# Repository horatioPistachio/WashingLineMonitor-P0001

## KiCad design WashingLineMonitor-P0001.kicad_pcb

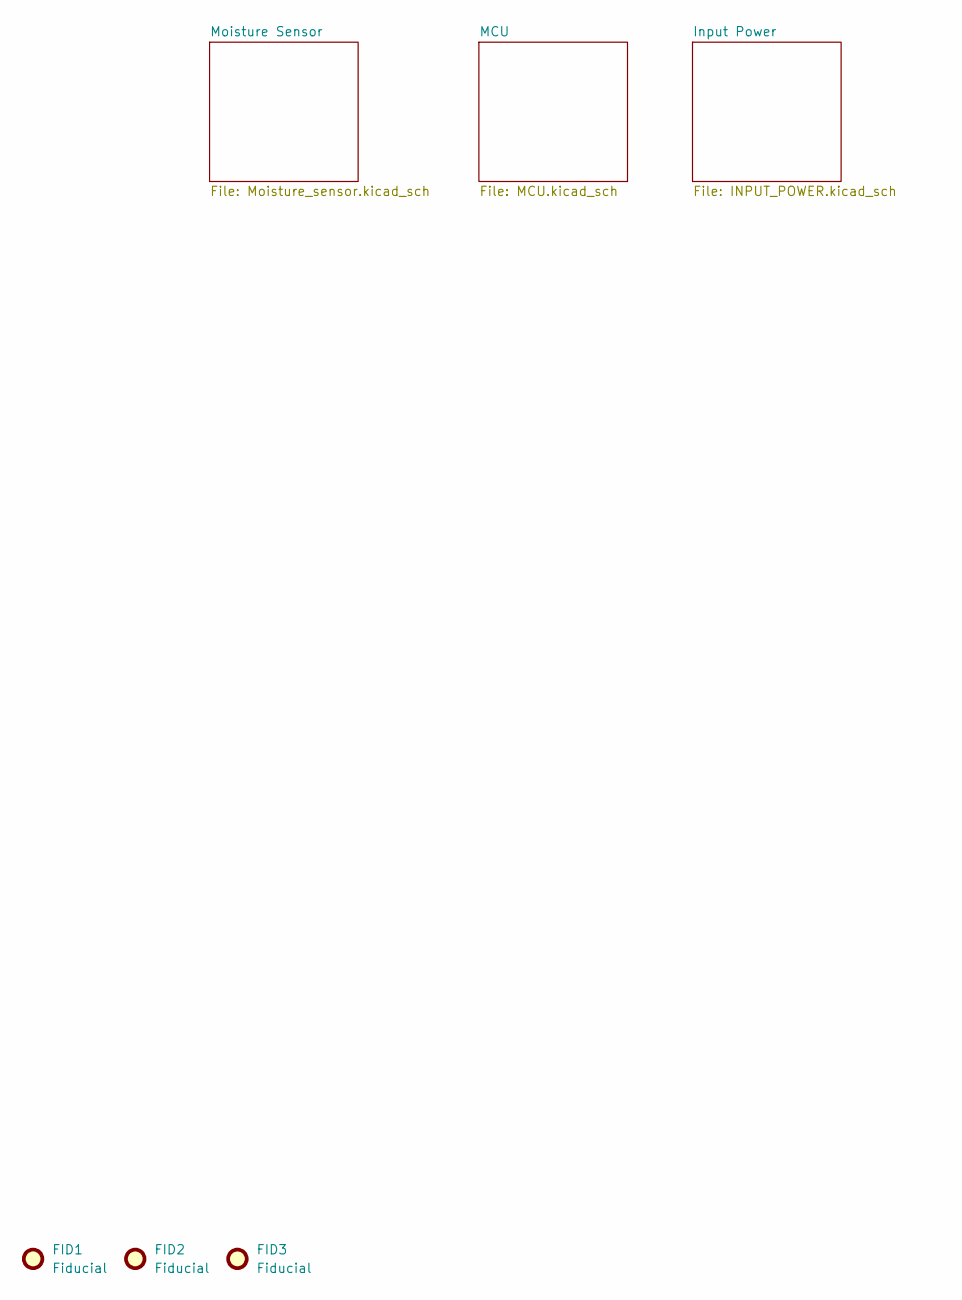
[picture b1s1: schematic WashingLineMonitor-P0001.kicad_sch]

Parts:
FID1, FID2, FID3: Fiducial; Fiducial_0.5mm_Mask1mm

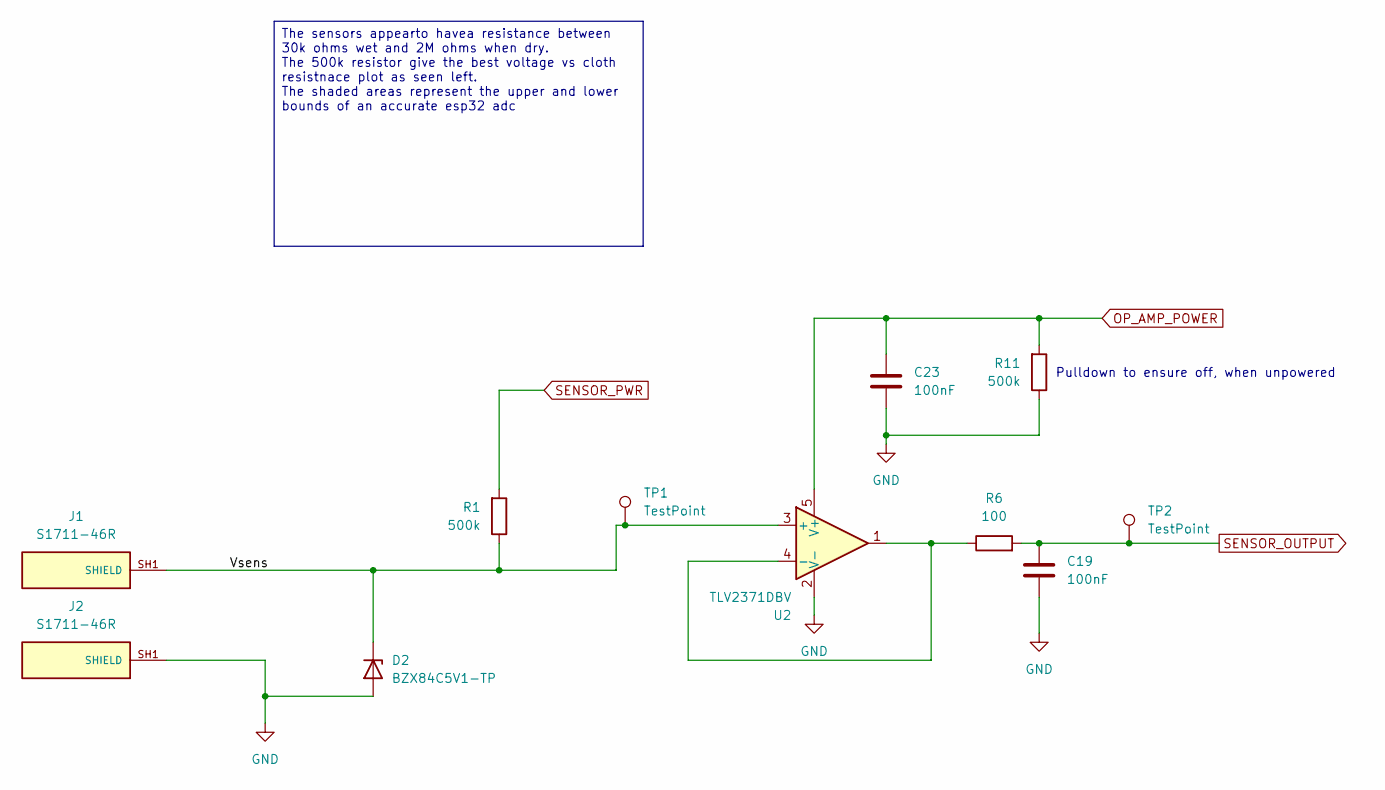
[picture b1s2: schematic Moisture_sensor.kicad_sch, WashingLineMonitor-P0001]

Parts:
C19, C23: 100nF; C_0805_2012Metric_Pad1.18x1.45mm_HandSolder
D2: BZX84C5V1-TP; SOT-23
J1, J2: S1711-46R; HARWIN_S1711-46R; PARTREV 8
R1, R11: 500k; R_0805_2012Metric_Pad1.20x1.40mm_HandSolder
R6: 100; R_0805_2012Metric_Pad1.20x1.40mm_HandSolder
TP1, TP2: TestPoint; TestPoint_Pad_D1.0mm
U2: TLV2371DBV; SOT-23-5

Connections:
/Moisture Sensor/Vsens: D2.3 (K), J1.SH1 (SHIELD_SH1), R1.1, TP1.1 (1_1), U2.3 (+)
GND: C19.2, C23.2, D2.1 (A), J2.SH1 (SHIELD_SH1), R11.1, U2.2 (V-); also elsewhere on the board
unnamed: R6.1, U2.1, U2.4 (-)
OP_AMP_POWER: C23.1, R11.2, U2.5 (V+); also elsewhere on the board
SENSOR_OUTPUT: C19.1, R6.2, TP2.1 (1_1); also elsewhere on the board
SENSOR_PWR: R1.2; also elsewhere on the board

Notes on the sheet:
Pulldown to ensure off, when unpowered
The sensors appearto havea resistance between 30k ohms wet and 2M ohms when dry. The 500k resistor give the best voltage vs cloth resistnace plot as seen left. The shaded areas represent the upper and lower bounds of an accurate esp32 adc

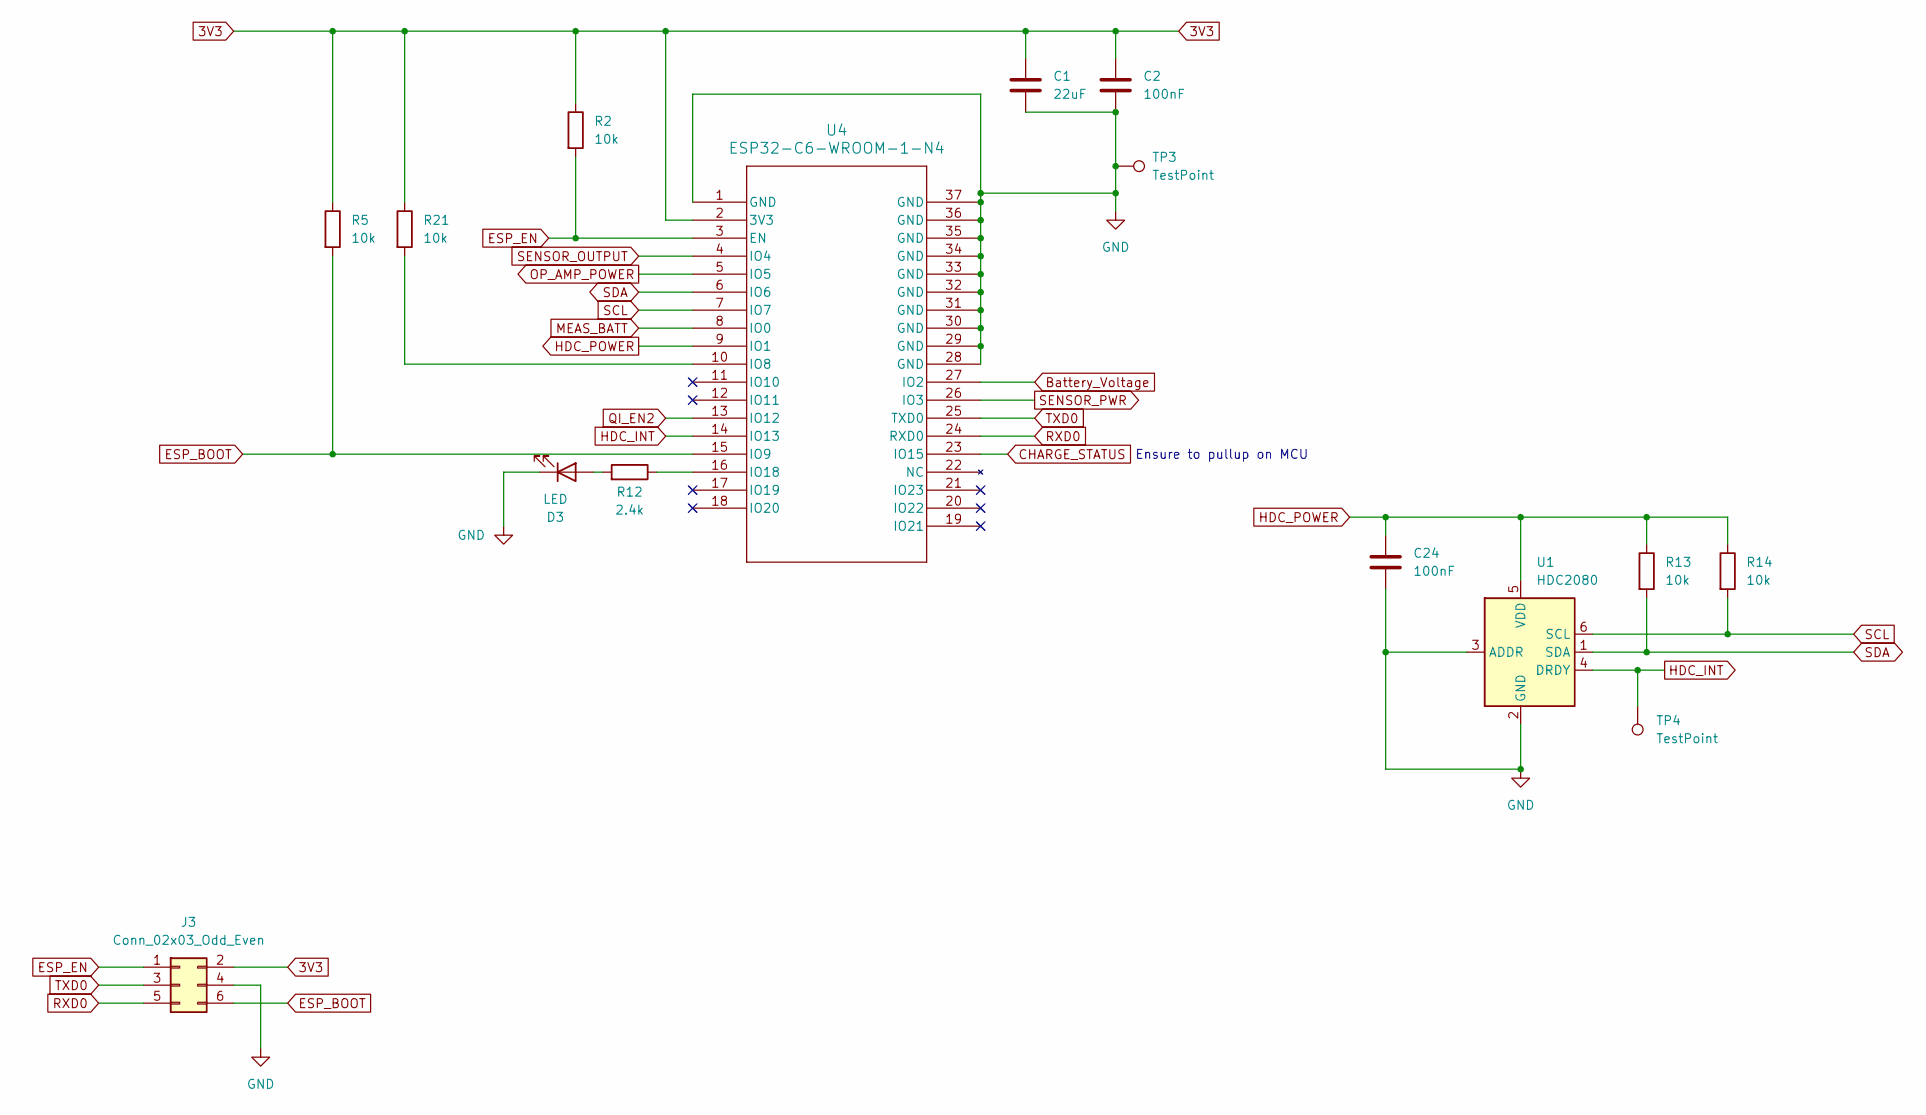
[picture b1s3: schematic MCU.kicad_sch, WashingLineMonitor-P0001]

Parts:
C1: 22uF; C_0805_2012Metric_Pad1.18x1.45mm_HandSolder
C2, C24: 100nF; C_0805_2012Metric_Pad1.18x1.45mm_HandSolder
D3: LED; LED_0805_2012Metric_Pad1.15x1.40mm_HandSolder
J3: Conn_02x03_Odd_Even; PinHeader_2x03_P1.27mm_Vertical_SMD; Digikey_Part_Number SAM13920TR-ND
R2, R5, R13, R14, R21: 10k; R_0805_2012Metric_Pad1.20x1.40mm_HandSolder
R12: 2.4k; R_0805_2012Metric_Pad1.20x1.40mm_HandSolder
TP3, TP4: TestPoint; TestPoint_Pad_D1.0mm
U1: HDC2080; Texas_S-PWSON-N6-HDC2080
U4: ESP32-C6-WROOM-1-N4; MOD28_ESP32-C6-WROOM-1_EXP

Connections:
3V3: C1.1, C2.1, J3.2, R2.1, R5.1, R21.1, U4.2 (3V3); also elsewhere on the board
Battery_Voltage: U4.27 (IO2); also elsewhere on the board
CHARGE_STATUS: U4.23 (IO15); also elsewhere on the board
ESP_BOOT: J3.6, R5.2, U4.15 (IO9)
ESP_EN: J3.1, R2.2, U4.3 (EN)
GND: C1.2, C2.2, C24.2, D3.1 (K), J3.4, TP3.1 (1_1), U1.2 (GND), U1.3 (ADDR), U4.1 (GND), U4.28 (GND), U4.29 (GND), U4.30 (GND), U4.31 (GND), U4.32 (GND), U4.33 (GND), U4.34 (GND), U4.35 (GND), U4.36 (GND), U4.37 (GND); also elsewhere on the board
HDC_INT: TP4.1 (1_1), U1.4 (DRDY), U4.14 (IO13)
HDC_POWER: C24.1, R13.1, R14.1, U1.5 (VDD), U4.9 (IO1)
MEAS_BATT: U4.8 (IO0); also elsewhere on the board
unnamed: D3.2 (A), R12.2
unnamed: R21.2, U4.10 (IO8)
unnamed: R12.1, U4.16 (IO18)
OP_AMP_POWER: U4.5 (IO5); also elsewhere on the board
QI_EN2: U4.13 (IO12); also elsewhere on the board
RXD0: J3.5, U4.24 (RXD0)
SCL: R14.2, U1.6 (SCL), U4.7 (IO7)
SDA: R13.2, U1.1 (SDA), U4.6 (IO6)
SENSOR_OUTPUT: U4.4 (IO4); also elsewhere on the board
SENSOR_PWR: U4.26 (IO3); also elsewhere on the board
TXD0: J3.3, U4.25 (TXD0)

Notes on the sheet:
Ensure to pullup on MCU

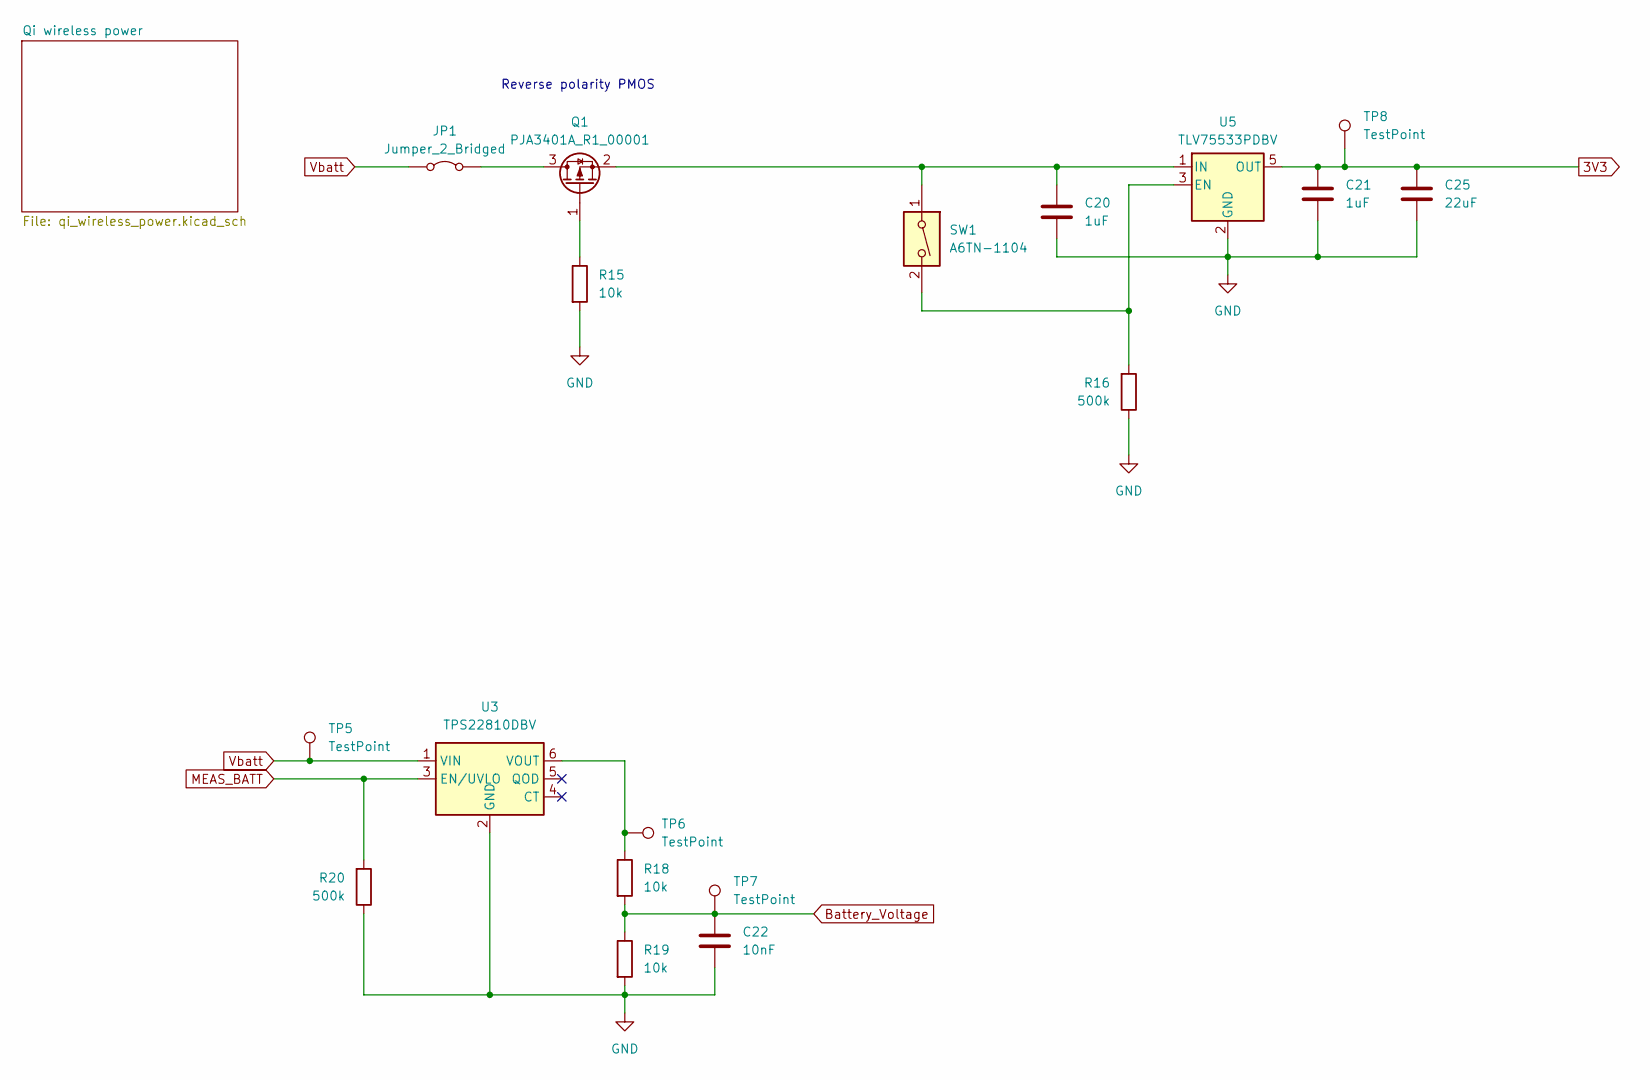
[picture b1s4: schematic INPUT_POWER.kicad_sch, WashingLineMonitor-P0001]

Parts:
C20, C21: 1uF; C_0805_2012Metric_Pad1.18x1.45mm_HandSolder
C22: 10nF; C_0805_2012Metric_Pad1.18x1.45mm_HandSolder
C25: 22uF; C_0805_2012Metric_Pad1.18x1.45mm_HandSolder
JP1: Jumper_2_Bridged; SolderJumper-2_P1.3mm_Bridged_RoundedPad1.0x1.5mm
Q1: PJA3401A_R1_00001; SOT-23
R15, R18, R19: 10k; R_0805_2012Metric_Pad1.20x1.40mm_HandSolder
R16, R20: 500k; R_0805_2012Metric_Pad1.20x1.40mm_HandSolder
SW1: A6TN-1104; SW_DIP_SPSTx01_Slide_6.7x4.1mm_W7.62mm_P2.54mm_LowProfile
TP5, TP6, TP7, TP8: TestPoint; TestPoint_Pad_D1.0mm
U3: TPS22810DBV; SOT-23-6
U5: TLV75533PDBV; SOT-23-5

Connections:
3V3: C21.2, C25.1, TP8.1 (1_1), U5.5 (OUT); also elsewhere on the board
Battery_Voltage: C22.1, R18.2, R19.1, TP7.1 (1_1); also elsewhere on the board
GND: C20.1, C21.1, C22.2, C25.2, R15.2, R16.1, R19.2, R20.1, U3.2 (GND), U5.2 (GND); also elsewhere on the board
MEAS_BATT: R20.2, U3.3 (EN/UVLO); also elsewhere on the board
unnamed: JP1.2 (B), Q1.3 (D)
unnamed: Q1.1 (G), R15.1
unnamed: C20.2, Q1.2 (S), SW1.1, U5.1 (IN)
unnamed: R18.1, TP6.1 (1_1), U3.6 (VOUT)
unnamed: R16.2, SW1.2, U5.3 (EN)
Vbatt: JP1.1 (A), TP5.1 (1_1), U3.1 (VIN); also elsewhere on the board

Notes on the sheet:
Reverse polarity PMOS

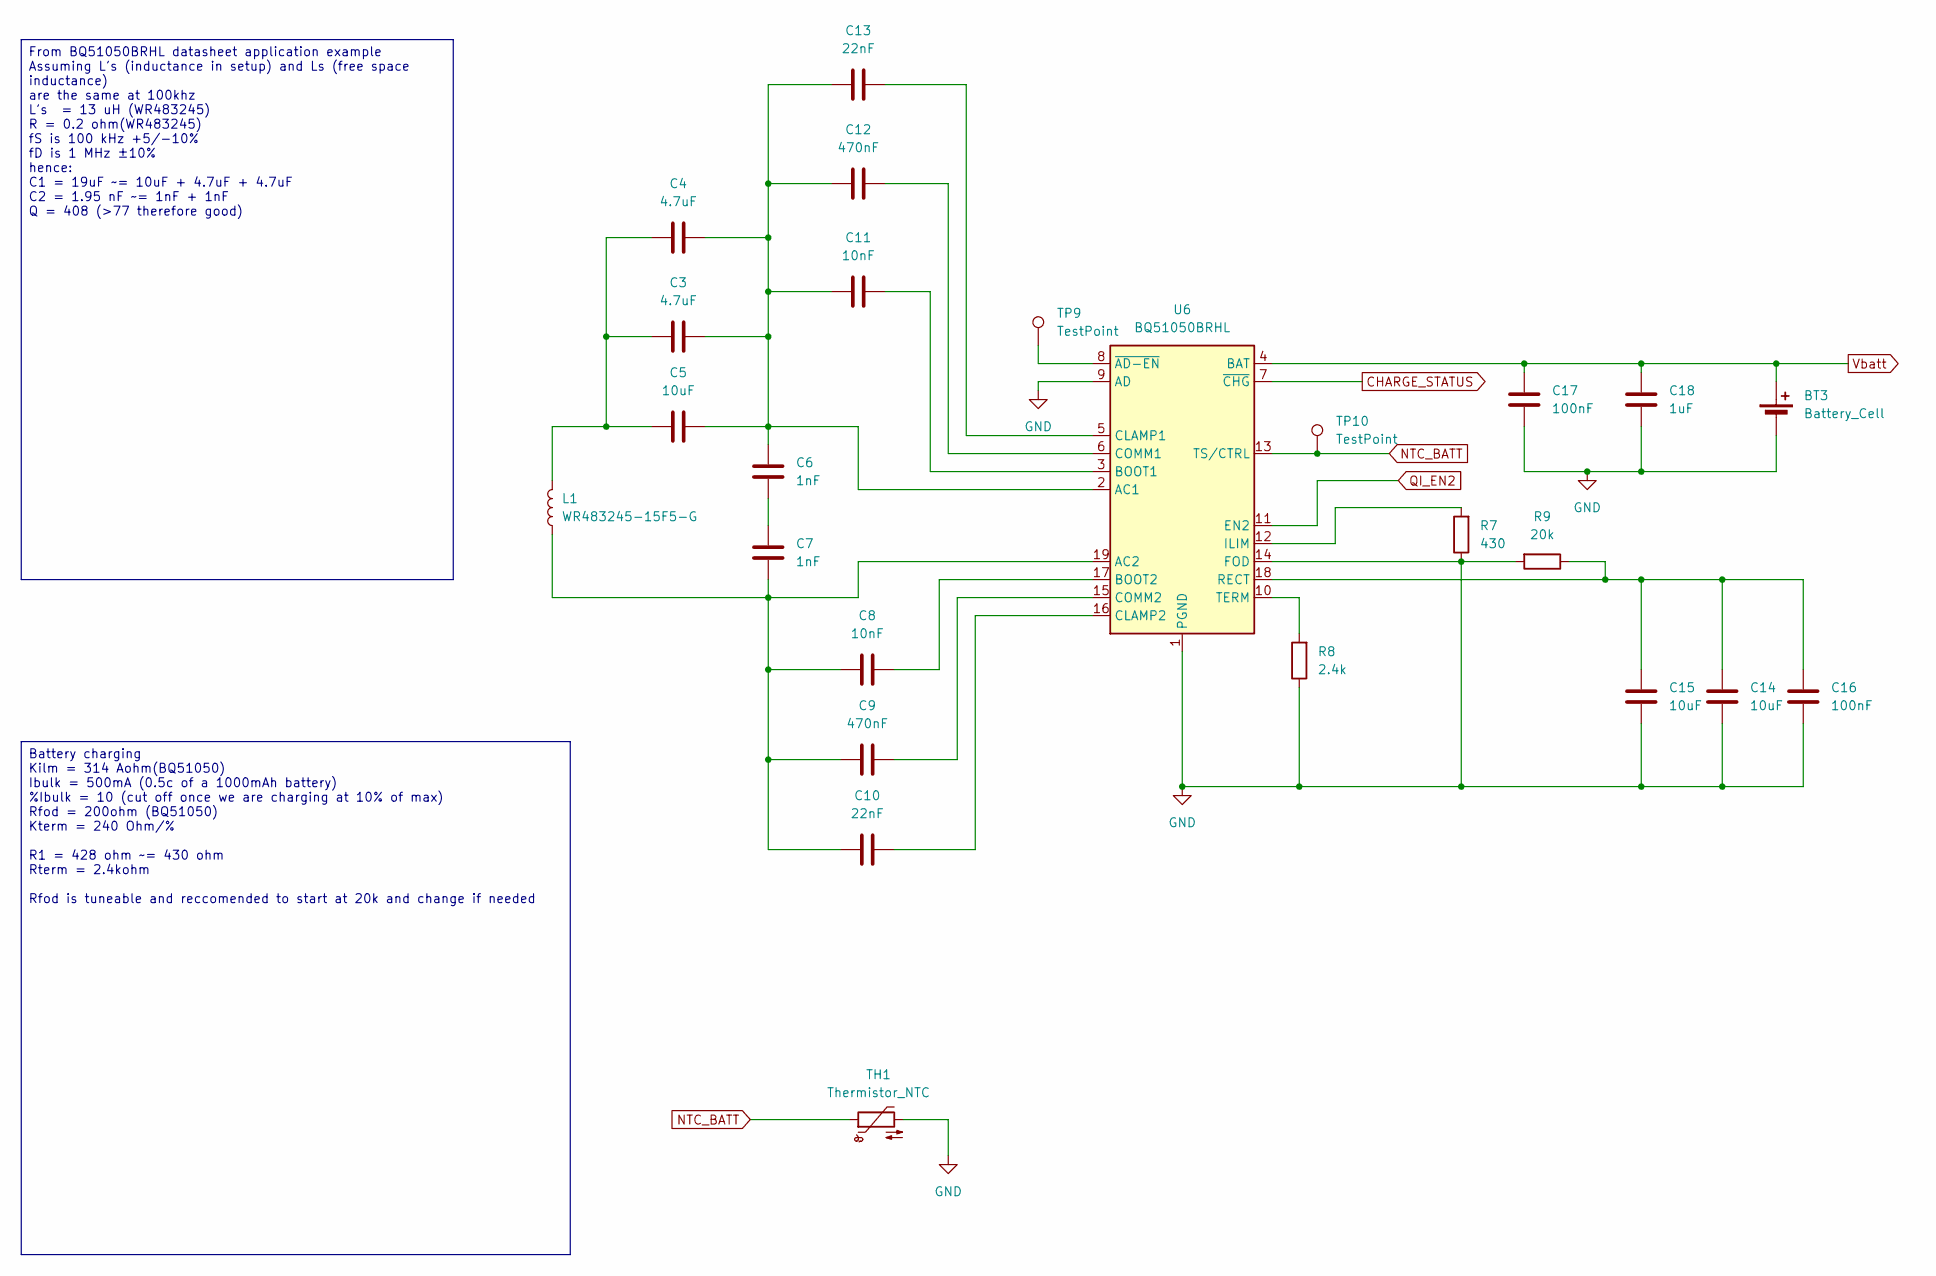
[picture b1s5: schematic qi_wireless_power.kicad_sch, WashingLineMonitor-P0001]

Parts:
BT3: Battery_Cell; JST_SH_SM02B-SRSS-TB_1x02-1MP_P1.00mm_Horizontal
C3, C4: 4.7uF; C_0805_2012Metric_Pad1.18x1.45mm_HandSolder
C5, C14, C15: 10uF; C_0805_2012Metric_Pad1.18x1.45mm_HandSolder
C6, C7: 1nF; C_0805_2012Metric_Pad1.18x1.45mm_HandSolder
C8, C11: 10nF; C_0805_2012Metric_Pad1.18x1.45mm_HandSolder
C9, C12: 470nF; C_0805_2012Metric_Pad1.18x1.45mm_HandSolder
C10, C13: 22nF; C_0805_2012Metric_Pad1.18x1.45mm_HandSolder
C16, C17: 100nF; C_0805_2012Metric_Pad1.18x1.45mm_HandSolder
C18: 1uF; C_0805_2012Metric_Pad1.18x1.45mm_HandSolder
L1: WR483245-15F5-G; JST_SH_SM02B-SRSS-TB_1x02-1MP_P1.00mm_Horizontal; JLC_Part_Number C5331042
R7: 430; R_0805_2012Metric_Pad1.20x1.40mm_HandSolder
R8: 2.4k; R_0805_2012Metric_Pad1.20x1.40mm_HandSolder
R9: 20k; R_0805_2012Metric_Pad1.20x1.40mm_HandSolder
TH1: Thermistor_NTC; R_0402_1005Metric_Pad0.72x0.64mm_HandSolder
TP9, TP10: TestPoint; TestPoint_Pad_D1.0mm
U6: BQ51050BRHL; Texas_VQFN-RHL-20; JLC_Part_Number C2650144

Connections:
CHARGE_STATUS: U6.7 (~CHG); also elsewhere on the board
GND: BT3.2 (-), C14.1, C15.1, C16.1, C17.1, C18.1, R7.1, R8.1, R9.2, TH1.2, U6.1 (PGND), U6.9 (AD), U6.14 (FOD), U6.20 (PGND), U6.21 (PGND); also elsewhere on the board
NTC_BATT: TH1.1, TP10.1 (1_1), U6.13 (TS/CTRL)
unnamed: C3.1, C4.1, C5.1, L1.2
unnamed: C6.1, C7.2
unnamed: C3.2, C4.2, C5.2, C6.2, C11.2, C12.2, C13.2, U6.2 (AC1)
unnamed: C7.1, C8.2, C9.2, C10.2, L1.1, U6.19 (AC2)
unnamed: C11.1, U6.3 (BOOT1)
unnamed: C8.1, U6.17 (BOOT2)
unnamed: C13.1, U6.5 (CLAMP1)
unnamed: C10.1, U6.16 (CLAMP2)
unnamed: C12.1, U6.6 (COMM1)
unnamed: C9.1, U6.15 (COMM2)
unnamed: R7.2, U6.12 (ILIM)
unnamed: C14.2, C15.2, C16.2, R9.1, U6.18 (RECT)
unnamed: R8.2, U6.10 (TERM)
unnamed: TP9.1 (1_1), U6.8 (~AD-EN)
QI_EN2: U6.11 (EN2); also elsewhere on the board
Vbatt: BT3.1 (+), C17.2, C18.2, U6.4 (BAT); also elsewhere on the board

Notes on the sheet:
Battery charging Kilm = 314 Aohm(BQ51050) Ibulk = 500mA (0.5c of a 1000mAh battery) %Ibulk = 10 (cut off once we are charging at 10% of max) Rfod = 200ohm (BQ51050) Kterm = 240 Ohm/% R1 = 428 ohm ~= 430 ohm Rterm = 2.4kohm Rfod is tuneable and reccomended to start at 20k and change if needed
From BQ51050BRHL datasheet application example Assuming L's (inductance in setup) and Ls (free space inductance) are the same at 100khz L's = 13 uH (WR483245) R = 0.2 ohm(WR483245) fS is 100 kHz +5/-10% fD is 1 MHz ±10% hence: C1 = 19uF ~= 10uF + 4.7uF + 4.7uF C2 = 1.95 nF ~= 1nF + 1nF Q = 408 (>77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

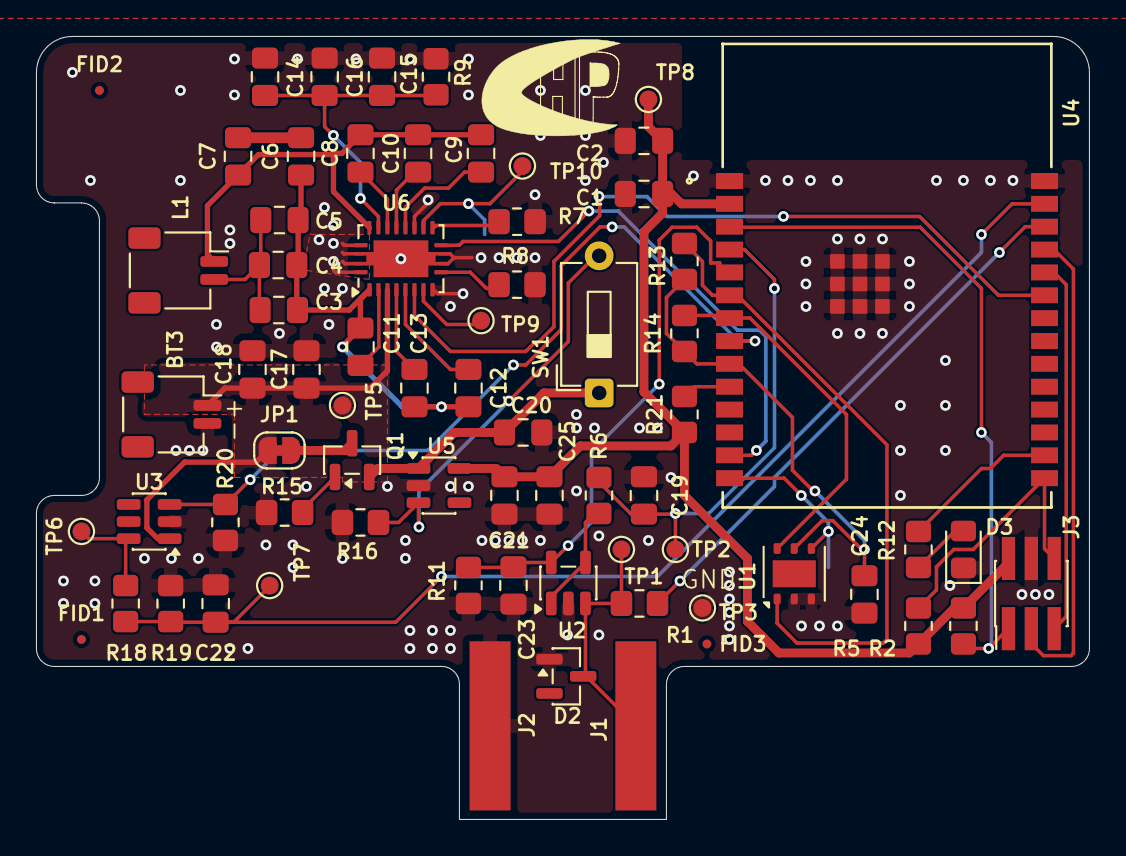
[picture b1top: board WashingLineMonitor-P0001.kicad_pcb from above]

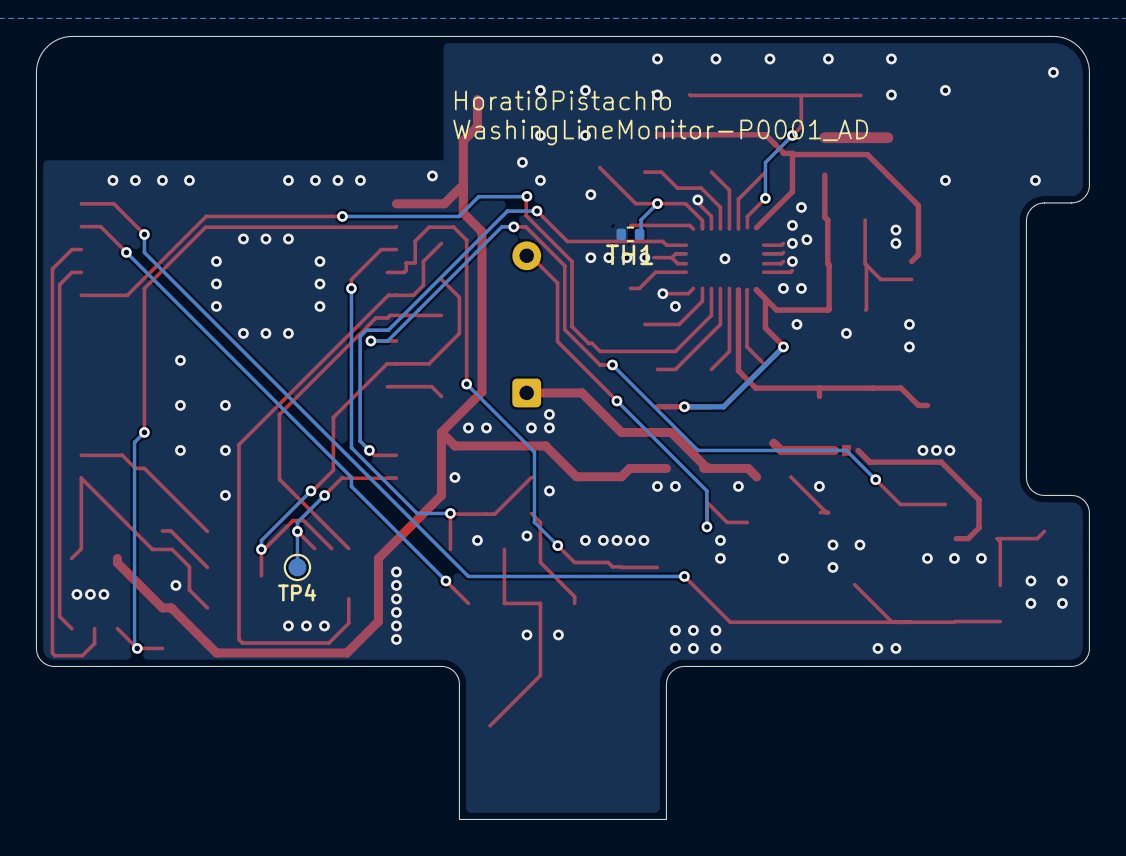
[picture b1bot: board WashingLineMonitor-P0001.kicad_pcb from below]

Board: 2 copper layers, 58.5 x 43.5 mm, 72 parts (2 on the bottom side), 43 nets.

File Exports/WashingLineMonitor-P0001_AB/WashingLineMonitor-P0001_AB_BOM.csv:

"Reference","Qty","Value","Footprint","Supplier","Supplier Part Number","DNP"
"3V3,AD-EN1,BattMeas1,GND1,SenseOut1,Vbatt1,Vsense1","7","TestPoint","TestPoint:TestPoint_Pad_D1.0mm","","",""
"BT3","1","Battery_Cell","Connector_Wire:SolderWire-0.1sqmm_1x02_P3.6mm_D0.4mm_OD1mm_Relief","Core Electronics","CE04377",""
"C1","1","22uF","Capacitor_SMD:C_0805_2012Metric_Pad1.18x1.45mm_HandSolder","Digikey","1276-CL21A226MAYNNNECT-ND",""
"C2,C16,C17,C19,C23","5","100nF","Capacitor_SMD:C_0805_2012Metric_Pad1.18x1.45mm_HandSolder","Digikey","1276-1003-1-ND",""
"C3,C4","2","4.7uF","Capacitor_SMD:C_0805_2012Metric_Pad1.18x1.45mm_HandSolder","Digikey","1276-1244-1-ND",""
"C5,C14,C15","3","10uF","Capacitor_SMD:C_0805_2012Metric_Pad1.18x1.45mm_HandSolder","Digikey","1276-1096-1-ND",""
"C6,C7","2","1nF","Capacitor_SMD:C_0805_2012Metric_Pad1.18x1.45mm_HandSolder","Digikey","1276-2425-1-ND",""
"C8,C11,C22","3","10nF","Capacitor_SMD:C_0805_2012Metric_Pad1.18x1.45mm_HandSolder","Digikey","1276-1015-1-ND",""
"C9,C12","2","470nF","Capacitor_SMD:C_0805_2012Metric_Pad1.18x1.45mm_HandSolder","Digikey","1276-6480-1-ND",""
"C10,C13","2","22nF","Capacitor_SMD:C_0805_2012Metric_Pad1.18x1.45mm_HandSolder","Digikey","1276-2488-1-ND",""
"C18,C20,C21","3","1uF","Capacitor_SMD:C_0805_2012Metric_Pad1.18x1.45mm_HandSolder","Digikey","1276-1029-1-ND",""
"D1","1","MBR0530","Diode_SMD:D_SOD-123","Digikey","1655-MBR0530CT-ND",""
"D2","1","BZX84C3V3-7-F","Package_TO_SOT_SMD:SOT-23","Digikey","BZX84C3V3-FDICT-ND",""
"J1","1","Conn_01x02_Socket","Connector_Wire:SolderWire-0.1sqmm_1x02_P3.6mm_D0.4mm_OD1mm_Relief","","",""
"J3","1","Conn_02x03_Odd_Even","Connector_PinHeader_1.27mm:PinHeader_2x03_P1.27mm_Vertical_SMD","Digikey","SAM13920TR-ND",""
"L1","1","WR483245-15F5-G","Connector_Wire:SolderWire-0.1sqmm_1x02_P3.6mm_D0.4mm_OD1mm_Relief","Digikey","445-16091-ND",""
"R1,R3,R4,R11","4","500k","Resistor_SMD:R_0805_2012Metric_Pad1.20x1.40mm_HandSolder","Digikey","738-RNCF0805BTE500KCT-ND",""
"R2,R5,R10","3","10k","Resistor_SMD:R_0805_2012Metric_Pad1.20x1.40mm_HandSolder","Digikey","P10KACT-ND",""
"R6","1","100","Resistor_SMD:R_0805_2012Metric_Pad1.20x1.40mm_HandSolder","Digikey","P100ACT-ND",""
"R7","1","430","Resistor_SMD:R_0805_2012Metric_Pad1.20x1.40mm_HandSolder","Digikey","P430DACT-ND",""
"R8","1","2.4k","Resistor_SMD:R_0805_2012Metric_Pad1.20x1.40mm_HandSolder","Digikey","P2.4KDACT-ND",""
"R9","1","20k","Resistor_SMD:R_0805_2012Metric_Pad1.20x1.40mm_HandSolder","Digikey","P20KACT-ND",""
"U1","1","ESP32-S2-SOLO-2-N4","Hydro_footprints:ESP32-S2-SOLO-N4","Digikey","1965-ESP32-S2-SOLO-2-N4CT-ND",""
"U2","1","TLV2371DBV","Package_TO_SOT_SMD:SOT-23-5","Digikey","296-13057-1-ND",""
"U4","1","AP2112K-3.3","Package_TO_SOT_SMD:SOT-23-5","Digikey","AP2112K-3.3TRG1DICT-ND",""
"U6","1","BQ51050BRHL","Package_DFN_QFN:Texas_VQFN-RHL-20","Digikey","296-BQ51050BRHLRCT-ND",""

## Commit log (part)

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2025-08-17 Added QI wireless charging circuit
2025-08-17 Added esp32-s2-solo module
2025-09-13 Completed first iteration and reviews
2025-09-14 added exports
2025-09-14 commited submodule
2025-09-14 Update KiCad PPA to use releases version
2025-09-14 updated export directory
2025-09-14 Update paths in release-artifacts workflow
2025-09-14 potential fix for actions issue
2025-09-14 another actions fix attempt
2025-09-14 fix slashing issue
2025-09-14 CI: checkout submodules recursively so export_kicad.py exists in Actions runner
2025-09-14 CI: add workflow_dispatch trigger for manual runs
2026-05-11 commit of local files before designing next version
2026-05-30 updated schematic from review
2026-05-30 laid out pcb
2026-06-04 Near complete AC
2026-06-06 Minor pre release changes
